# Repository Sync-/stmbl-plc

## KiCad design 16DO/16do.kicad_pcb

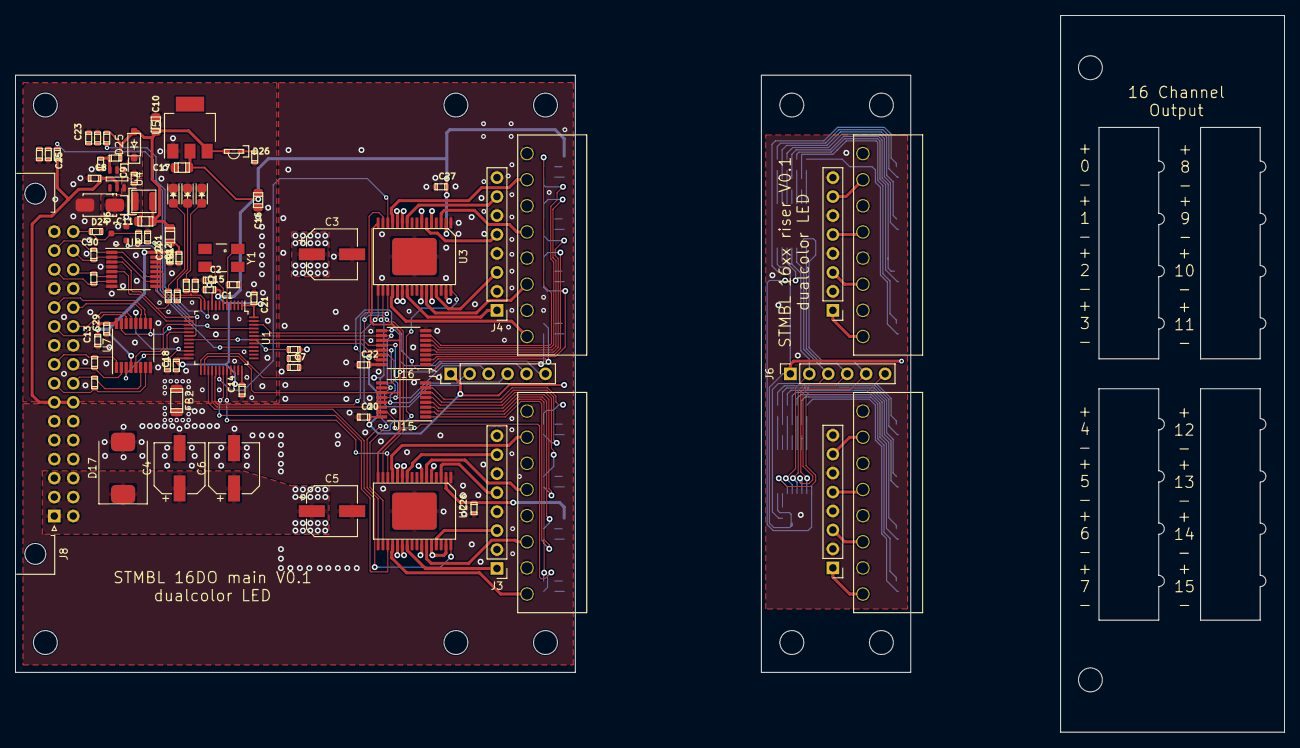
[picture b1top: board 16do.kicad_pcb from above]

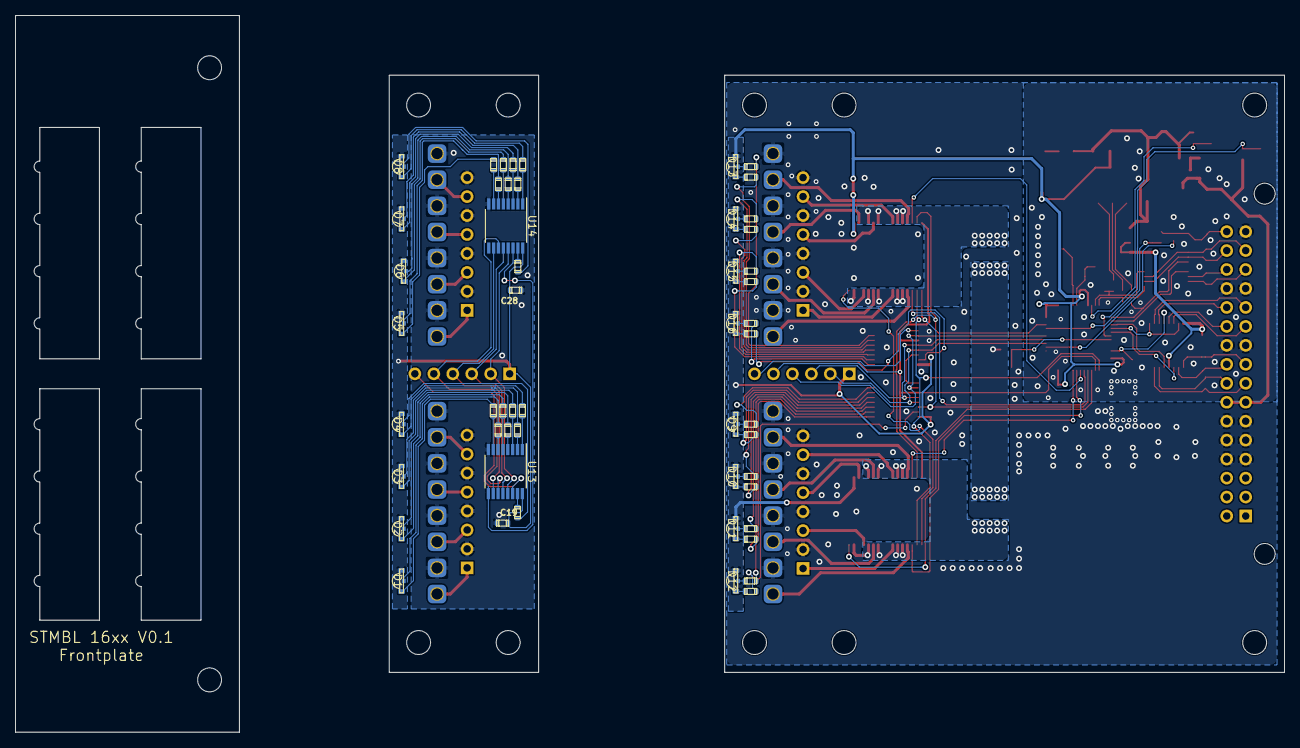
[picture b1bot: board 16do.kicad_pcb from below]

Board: 2 copper layers, 170.0 x 96.0 mm, 144 parts (52 on the bottom side), 143 nets.

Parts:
C1, C2: 18p; C_0603
C3, C4, C5, C6: 100µ; CP_Elec_6.3x7.7
C7, C8, C9, C12, C13, C14, C18, C19, C20, C21, C22, C23, C24, C25, C26, C27, C28, C29: 100n; C_0603
C10, C11: 10u; C_0805
C15: 2.2µ; C_0603
C16, C17: 10µ; C_0805
C30, C31: 1n; C_0603
D1, D2, D3, D4, D5, D6, D7, D8, D9, D10, D11, D12, D13, D14, D15, D16: LED_Dual_CCA; LED1206Duo-SIDE
D17: 1.5KExxA; D_SMC
D21, D22, D23: LED; LED-0805
D24: ss110; SMA_Standard
D25: 1N4148; SOD-123
D26: Led_Small; LED-0805-SIDE
FB1: Ferrite_Bead_Small; C_0805
FB2: Ferrite_Bead_Small; C_1206
J2, J3, J4, J5: CONN_01X16; PinHeader_1x08_P2.54mm_Vertical
J6: CONN_01X06; PinSocket_1x06_P2.54mm_Vertical
J7: CONN_01X06; PinHeader_1x06_P2.54mm_Vertical
J8: Conn_02x16_Row_Letter_First; DIN41612_B2_2x16_Horizontal
L1: 22µ 650mA; SMD_INDUCTOR_32x25
MK1, MK2, MK3, MK4, MK5, MK6, MK7, MK8, MK9, MK10, MK11, MK12: Mounting_Hole; MountingHole_3.2mm_M3
P1, P2, P3, P4: CONN_01X08; RM3.5_1x8
R2, R50, R52, R53, R54, R55: 1k; R_0603
R3, R4, R7, R8, R9, R10, R11, R12, R13, R14, R15, R16, R17, R18, R19, R20, R21, R22, R23, R24, R25, R26, R27, R28, R29, R30, R31, R32, R33, R34, R35, R36, R37, R38, R39, R40, R41, R44, R45, R48, R49: R; R_0603
R42: 51k; R_0603
R43: 10k; R_0603
R46: 470; R_0603
R51: 120; R_0603
U1: STM32F030CCTx; LQFP-48_7x7mm_P0.5mm
U2, U3: MC33879A; SOICW_32_EPAD
U4: MCP16331; SOT-23-6
U5: AP1117-33; SOT-223-3_TabPin2
U6: NFET; SOT-23
U7, U8: ADM4168E; TSSOP-16_4.4x5mm_P0.65mm
U13, U14, U15, U16: 74HC595; TSSOP-16_4.4x5mm_P0.65mm
Y1: Crystal_GND3; Crystal_SMD_0603_4Pads

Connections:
+3V3: C14.1, C15.1, C16.1, C17.1, C18.1, C19.1, C20.1, C21.1, C22.1, C26.1, C27.1, C28.1, D1.3, D2.3, D3.3, D4.3, D5.3, D6.3, D7.3, D8.3, D9.3, D10.3, D11.3, D12.3, D13.3, D14.3, D15.3, D16.3, J6.1, J7.1, U1.1, U1.9, U1.24, U1.36, U1.48, U2.2, U3.2, U5.2, U13.16, U14.16, U15.16, U16.16
+5V: C10.1, C11.1, D25.2, D26.2, FB1.1, L1.2, R42.1, R44.1, U5.3
+5VL: C12.1, C13.1, C24.1, C29.1, FB1.2, U7.4, U7.16, U8.16
+24V: C8.1, J8.a7, J8.b7, R48.1, U4.5
+VDC: C3.1, C4.1, C5.1, C6.1, D17.1, J8.a1, J8.a2, J8.a3, J8.b1, J8.b2, J8.b3, R3.1, U2.5, U2.7, U2.11, U2.12, U2.21, U2.22, U2.26, U2.28, U2.31, U3.5, U3.7, U3.11, U3.12, U3.21, U3.22, U3.26, U3.28, U3.31
/Power Supply/BOOST: C9.1, D25.1, U4.1
/Power Supply/FB: R42.2, R43.1, U4.3
/Power Supply/SW: C9.2, D24.1, L1.1, U4.6
AIN1: C23.2, R44.2, R45.1, U1.10
AIN2: C25.2, R48.2, R49.1, U1.18
AIN3: C7.2, R3.2, R4.1, U1.19
DSPI_CS: U1.14, U8.5
DSPI_MISO: U1.16, U7.9, U7.15
DSPI_MOSI: U1.17, U7.3
DSPI_SCK: U1.15, U7.5
DSPI_TXEN: R55.1, U1.22, U7.12
EN_OUT: U1.46, U2.15, U3.15
EST: C30.1, J8.b16, R50.2, U6.3
ESTOP_IN: C31.1, R50.1, U1.45
ESTOP_OUT: U1.40, U6.1
GND: C1.2, C2.2, C8.2, C10.2, C11.2, C12.2, C13.2, C14.2, C15.2, C16.2, C17.2, C18.2, C21.2, C23.1, C24.2, C25.1, C29.2, C30.2, C31.2, D21.1, D22.1, D23.1, D24.2, FB2.1, J8.a10, J8.a13, J8.a16, J8.b10, J8.b13, R43.2, R45.2, R46.2, R49.2, R54.2, R55.2, U1.8, U1.23, U1.35, U1.47, U4.2, U5.1, U6.2, U7.8, U8.4, U8.8
GNDPWR: C3.2, C4.2, C5.2, C6.2, C7.1, C19.2, C20.2, C22.2, C26.2, C27.2, C28.2, D17.2, FB2.2, J2.2, J2.4, J2.6, J2.8, J3.2, J3.4, J3.6, J3.8, J4.2, J4.4, J4.6, J4.8, J5.2, J5.4, J5.6, J5.8, J8.a4, J8.a5, J8.a6, J8.b4, J8.b5, J8.b6, P1.2, P1.4, P1.6, P1.8, P2.2, P2.4, P2.6, P2.8, P3.2, P3.4, P3.6, P3.8, P4.2, P4.4, P4.6, P4.8, R4.2, U2.1, U2.33, U3.1, U3.33, U13.8, U14.8, U15.8, U16.8
LCS+: J8.b14, R53.1, U8.6
LCS-: J8.a14, R53.2, U8.7
LMI+: J8.a12, U7.10
LMI-: J8.b12, U7.11
LSC+: J8.b8, R51.2, U7.6
LSC-: J8.a8, R51.1, U7.7
LSI+: J8.b9, R52.2, U7.2
LSI-: J8.a9, R52.1, U7.1
LSO+: J8.a11, U7.14
LSO-: J8.b11, U7.13
unnamed: C1.1, U1.5, Y1.1
unnamed: C2.1, U1.6, Y1.2
unnamed: D1.1, R16.1
unnamed: D1.2, R15.1
unnamed: D2.1, R14.1
unnamed: D2.2, R13.1
unnamed: D3.1, R12.1
unnamed: D3.2, R11.1
unnamed: D4.1, R10.1
unnamed: D4.2, R9.1
unnamed: D5.1, R24.1
unnamed: D5.2, R23.1
unnamed: D6.1, R22.1
unnamed: D6.2, R21.1
unnamed: D7.1, R20.1
unnamed: D7.2, R19.1
unnamed: D8.1, R18.1
unnamed: D8.2, R17.1
unnamed: D9.1, R26.1
unnamed: D9.2, R25.1
unnamed: D10.1, R28.1
unnamed: D10.2, R27.1
unnamed: D11.1, R30.1
unnamed: D11.2, R29.1
unnamed: D12.1, R32.1
unnamed: D12.2, R31.1
unnamed: D13.1, R34.1
unnamed: D13.2, R33.1
unnamed: D14.1, R36.1
unnamed: D14.2, R35.1
unnamed: D15.1, R38.1
unnamed: D15.2, R37.1
unnamed: D16.1, R40.1
unnamed: D16.2, R39.1
unnamed: D21.2, R7.2
unnamed: D22.2, R8.2
unnamed: D23.2, R41.2
unnamed: D26.1, R46.1
unnamed: J6.2, U13.13, U14.13
unnamed: J6.3, U13.12, U14.12
unnamed: J6.4, U13.10, U14.10
unnamed: J6.5, U13.11, U14.11
unnamed: J6.6, U13.14
unnamed: J7.6, U16.9
unnamed: R9.2, U13.15
unnamed: R10.2, U13.1
unnamed: R11.2, U13.2
unnamed: R12.2, U13.3
unnamed: R13.2, U13.4
unnamed: R14.2, U13.5
unnamed: R15.2, U13.6
unnamed: R16.2, U13.7
unnamed: R17.2, U14.15
unnamed: R18.2, U14.1
unnamed: R19.2, U14.2
unnamed: R20.2, U14.3
unnamed: R21.2, U14.4
unnamed: R22.2, U14.5
unnamed: R23.2, U14.6
unnamed: R24.2, U14.7
unnamed: R25.2, U15.7
unnamed: R26.2, U15.6
unnamed: R27.2, U15.5
unnamed: R28.2, U15.4
unnamed: R29.2, U15.3
unnamed: R30.2, U15.2
unnamed: R31.2, U15.1
unnamed: R32.2, U15.15
unnamed: R33.2, U16.7
unnamed: R34.2, U16.6
unnamed: R35.2, U16.5
unnamed: R36.2, U16.4
unnamed: R37.2, U16.3
unnamed: R38.2, U16.2
unnamed: R39.2, U16.1
unnamed: R40.2, U16.15
unnamed: U2.17, U3.32
unnamed: U13.9, U14.14
unnamed: U15.9, U16.14
OE: J7.2, U1.41, U15.13, U16.13
OUT0: P1.1, U2.20
OUT1: P1.3, U2.27
OUT2: P1.5, U2.6
OUT3: P1.7, U2.13
OUT4: P2.1, U3.20
OUT5: P2.3, U3.27
OUT6: P2.5, U3.3
OUT7: P2.7, U3.13
OUT8: J4.1, J5.1, P3.1, U3.23
OUT9: J4.3, J5.3, P3.3, U3.29
OUT10: J4.5, J5.5, P3.5, U3.6
OUT11: J4.7, J5.7, P3.7, U3.10
OUT12: J2.1, J3.1, P4.1, U2.23
OUT13: J2.3, J3.3, P4.3, U2.29
OUT14: J2.5, J3.5, P4.5, U2.3
OUT15: J2.7, J3.7, P4.7, U2.10
PWM0: U1.29, U3.19
PWM1: U1.30, U3.14
PWM2: U1.31, U2.19
PWM3: U1.32, U2.14
RCLK: J7.3, U1.42, U15.12, U16.12
SPI2_CS: U1.25, U2.18, U3.18
SPI2_MISO: U1.27, U2.32
SPI2_MOSI: U1.28, U3.17, U15.14
SPI2_SCK: J7.5, U1.26, U2.16, U3.16, U15.11, U16.11
SRCLR: J7.4, U1.43, U15.10, U16.10
UA1+: J8.b15, R2.1, U8.2, U8.10
UA1-: J8.a15, R2.2, U8.1, U8.11
USART_EN: R41.1, R54.1, U1.11, U8.12
USART_RX: R7.1, U1.13, U8.3
USART_TX: R8.1, U1.12, U8.9

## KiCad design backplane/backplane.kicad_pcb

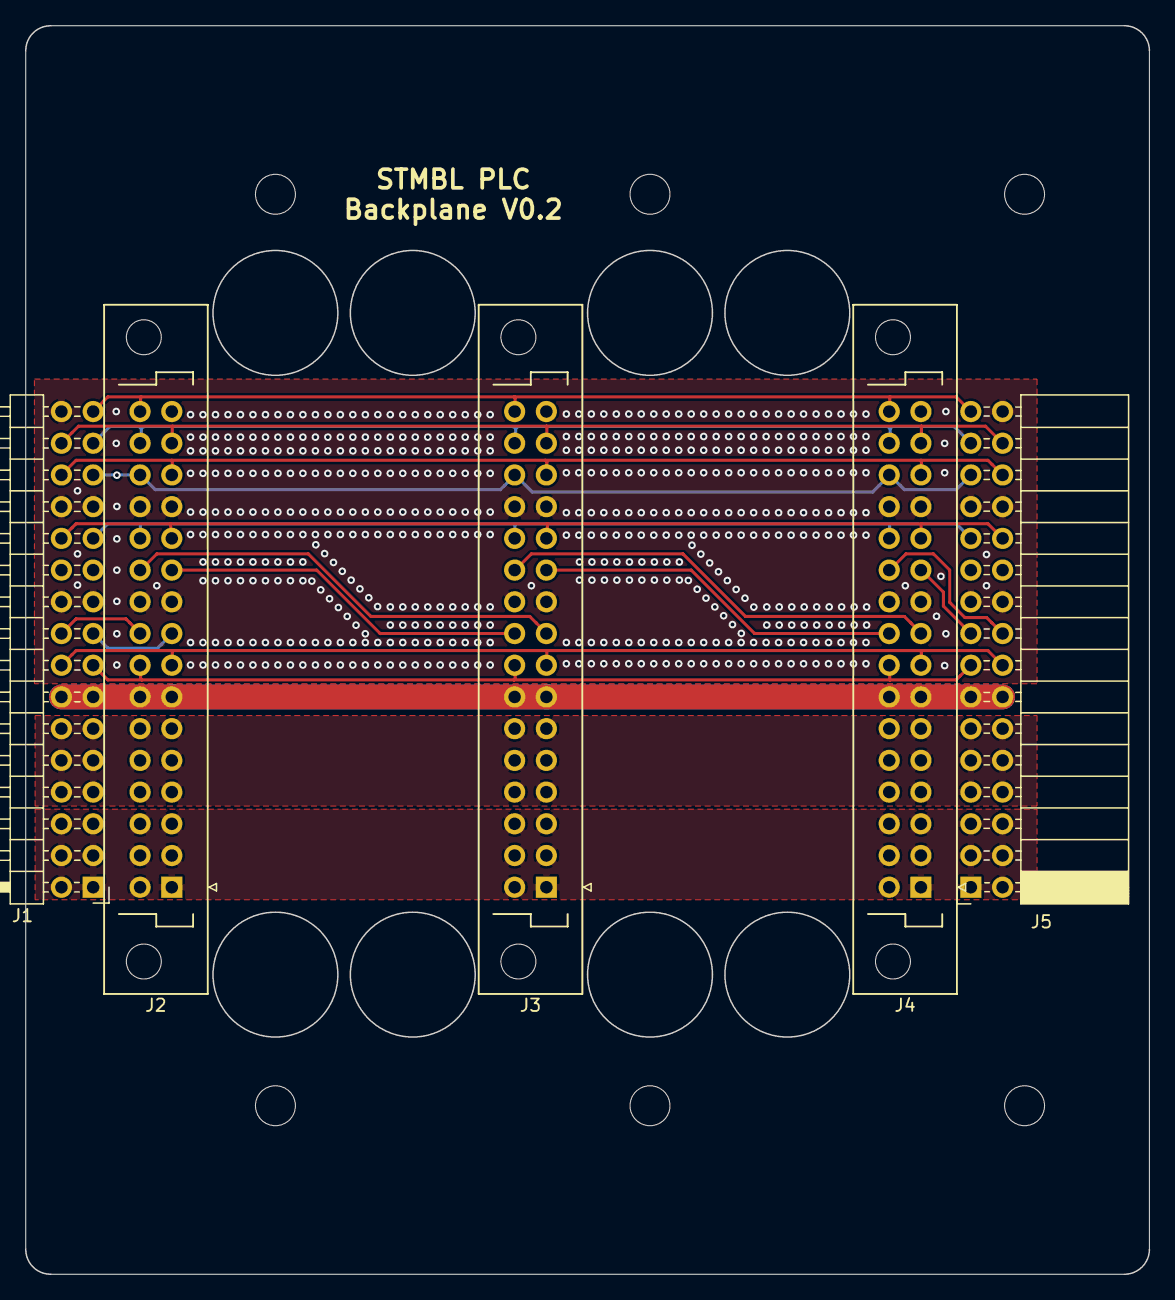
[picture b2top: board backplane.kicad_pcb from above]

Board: 2 copper layers, 90.0 x 100.0 mm, 11 parts (0 on the bottom side), 21 nets.

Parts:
J1: Conn_02x16_Row_Letter_First; PinHeader_2x16_P2.54mm_Horizontal
J2, J3, J4: Conn_02x16_Row_Letter_First; DIN41612_B2_2x16_Vertical
J5: Conn_02x16_Row_Letter_First; PinSocket_2x16_P2.54mm_Horizontal
MK1, MK2, MK3, MK4, MK5, MK6: Mounting_Hole; MountingHole_3.2mm_M3

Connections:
+24V: J1.13, J1.14, J2.a7, J2.b7, J3.a7, J3.b7, J4.a7, J4.b7, J5.13, J5.14
EST: J1.31, J2.b16, J3.b16, J4.b16, J5.31
GND: J1.19, J1.20, J1.25, J1.26, J1.32, J2.a10, J2.a13, J2.a16, J2.b10, J2.b13, J3.a10, J3.a13, J3.a16, J3.b10, J3.b13, J4.a10, J4.a13, J4.a16, J4.b10, J4.b13, J5.19, J5.20, J5.25, J5.26, J5.32
GNDPWR: J1.7, J1.8, J1.9, J1.10, J1.11, J1.12, J2.a4, J2.a5, J2.a6, J2.b4, J2.b5, J2.b6, J3.a4, J3.a5, J3.a6, J3.b4, J3.b5, J3.b6, J4.a4, J4.a5, J4.a6, J4.b4, J4.b5, J4.b6, J5.7, J5.8, J5.9, J5.10, J5.11, J5.12
LCS+: J1.27, J2.b14, J3.b14, J4.b14, J5.27
LCS-: J1.28, J2.a14, J3.a14, J4.a14, J5.28
LMI+: J1.24, J2.a12, J3.a12, J4.a12, J5.24
LMI-: J1.23, J2.b12, J3.b12, J4.b12, J5.23
LSC+: J1.15, J2.b8, J3.b8, J4.b8, J5.15
LSC-: J1.16, J2.a8, J3.a8, J4.a8, J5.16
unnamed: J1.17, J2.a9
unnamed: J1.18, J2.b9
unnamed: J2.a11, J3.b9
unnamed: J2.b11, J3.a9
unnamed: J3.a11, J4.b9
unnamed: J3.b11, J4.a9
unnamed: J4.a11, J5.17
unnamed: J4.b11, J5.18
UA1+: J1.29, J2.b15, J3.b15, J4.b15, J5.29
UA1-: J1.30, J2.a15, J3.a15, J4.a15, J5.30
VDC: J1.1, J1.2, J1.3, J1.4, J1.5, J1.6, J2.a1, J2.a2, J2.a3, J2.b1, J2.b2, J2.b3, J3.a1, J3.a2, J3.a3, J3.b1, J3.b2, J3.b3, J4.a1, J4.a2, J4.a3, J4.b1, J4.b2, J4.b3, J5.1, J5.2, J5.3, J5.4, J5.5, J5.6

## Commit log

2018-08-12 Stuff and things
2019-02-23 add dual color leds, finalize formfactor
2019-02-24 add backplane
2019-02-24 add diff spi, rs485, started routing
2019-04-05 move right side by 10mm so you can actually chain stuff
2019-04-06 finish leds, route most stuff
2019-04-07 stuff to do
2019-04-08 todo foo
2019-04-12 change over to plc bus
2019-04-18 routing
2019-04-18 adjust backplane to new spec
2019-05-18 finish routing and change comms schematic to backplane spec
2019-09-24 Update TODO
